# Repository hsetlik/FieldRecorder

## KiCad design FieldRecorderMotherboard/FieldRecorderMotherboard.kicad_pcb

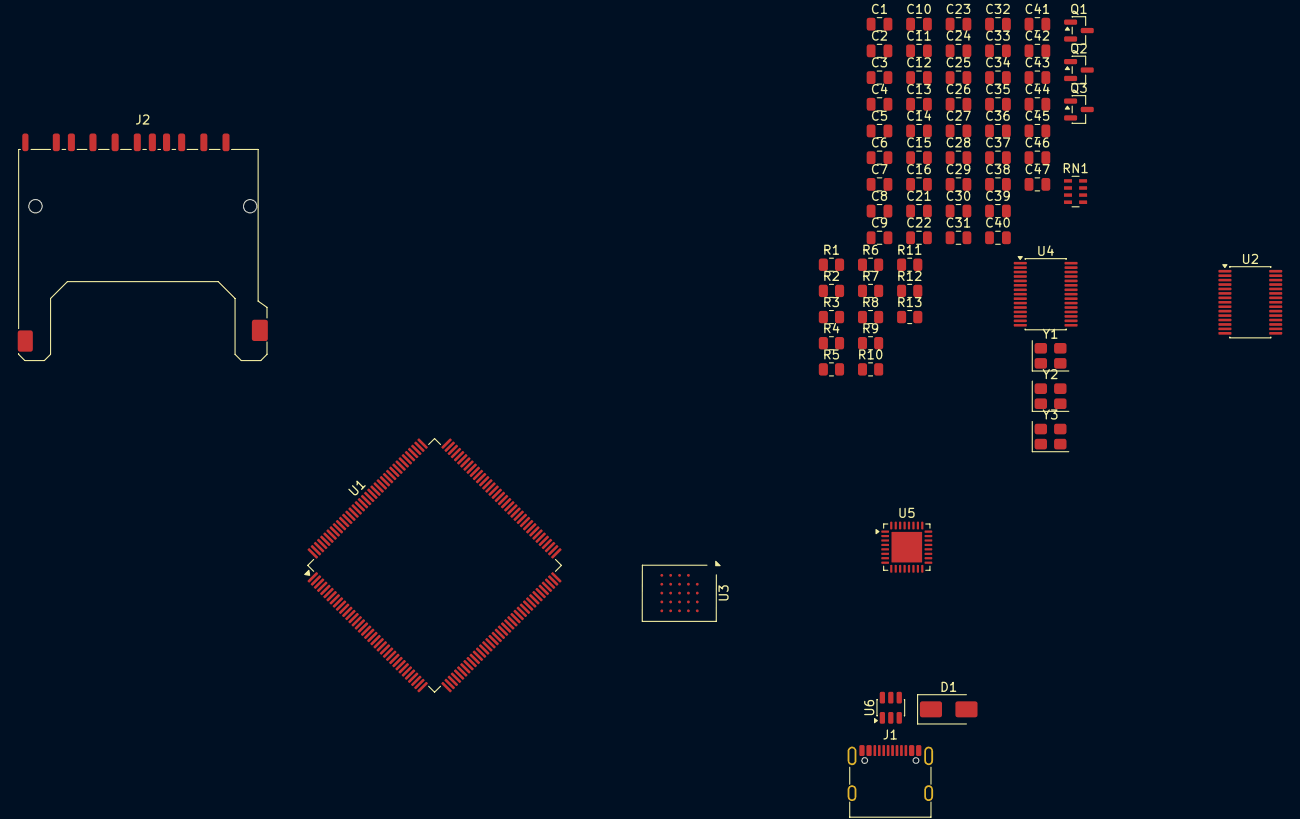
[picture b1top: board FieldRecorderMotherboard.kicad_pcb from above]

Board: 2 copper layers, 72 parts (0 on the bottom side), 67 nets, no tracks yet.

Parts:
C1, C4, C6, C9, C11, C12, C13, C14, C25, C26, C27, C28, C31, C32, C34, C35, C36, C37, C38, C39, C40, C41, C42, C43, C44, C45, C46: 1u; C_0805_2012Metric
C2, C7: 100n; C_0805_2012Metric
C3, C5, C8, C10, C47: 10u; C_0805_2012Metric
C15, C16: 2u2; C_0805_2012Metric
C21, C22, C23, C24, C29, C30: 6p; C_0805_2012Metric
C33: 4n7; C_0805_2012Metric
D1: SMAJ5.0A; D_SMA
J1: USB_C_Receptacle_USB2.0_16P; USB_C_Receptacle_G-Switch_GT-USB-7010ASV
J2: SD_Card_Receptacle; SD_Kyocera_145638009211859+
Q1: MMFTP3401; SOT-23
Q2, Q3: 2N7002; SOT-23
R1, R2: 2k2; R_0805_2012Metric
R3: 12.0k 1%; R_0805_2012Metric
R4: 820; R_0805_2012Metric
R5, R6: 5k1; R_0805_2012Metric
R7: 1Meg; R_0805_2012Metric
R8: 0R; R_0805_2012Metric
R9: 47; R_0805_2012Metric
R10: 100k; R_0805_2012Metric
R11: 100; R_0805_2012Metric
R12, R13: 22k; R_0805_2012Metric
RN1: 22k; R_Array_Concave_4x0603
U1: STM32H723ZGTx; LQFP-144_20x20mm_P0.5mm
U2, U4: PCM1864DBT; TSSOP-30_4.4x7.8mm_P0.5mm
U3: APS12808L; miniBGA-24_6x8mm_Layout5x5_P1.0mm
U5: USB3300-EZK; QFN-32-1EP_5x5mm_P0.5mm_EP3.45x3.45mm
U6: USBLC6-2SC6; SOT-23-6
Y1, Y2: 16MHz; Crystal_SMD_3225-4Pin_3.2x2.5mm
Y3: 24Mhz; Crystal_SMD_3225-4Pin_3.2x2.5mm

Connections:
+3.3V: C4.1, C5.1, C9.1, C10.1, C13.1, C14.1, C25.2, C26.2, C34.2, C35.2, C36.2, C37.2, C38.2, C39.2, C40.2, C41.2, C42.2, C43.2, C44.2, C45.2, Q1.3 (D), R1.1, R2.1, R9.1, R10.1, R13.1, U1.6 (VBAT), U1.17 (VDD), U1.30 (VDD), U1.39 (VDD), U1.52 (VDD), U1.62 (VDD), U1.72 (VDD), U1.84 (VDD), U1.95 (VDD33USB), U1.108 (VDD), U1.121 (VDD), U1.131 (VDD), U1.144 (VDD), U2.13 (DVDD), U2.14 (IOVDD), U3.B4 (VDD), U3.D1 (VDDQ), U3.E4 (VDDQ), U4.13 (DVDD), U4.14 (IOVDD), U4.25 (MS/AD), U5.6 (VDD3.3), U5.16 (VDD3.3), U5.25 (VDD3.3), U5.30 (VDD3.3), U5.31 (REG_EN)
+3.3VA: C1.1, C6.1, C46.2, C47.2, R9.2, U1.33 (VDDA), U2.8 (AVDD), U4.8 (AVDD)
/AudioMCU/ADC_BCK: U1.4 (PE5), U2.17 (BCK), U4.17 (BCK)
/AudioMCU/ADC_DATA: U1.5 (PE6), U2.18 (DOUT), U4.18 (DOUT)
/AudioMCU/ADC_LRCK: U1.3 (PE4), U2.16 (LRCK), U4.16 (LRCK)
/AudioMCU/ADC_SCL: R1.2, U1.136 (PB6), U2.24 (MC/SCL), U4.24 (MC/SCL)
/AudioMCU/ADC_SDA: R2.2, U1.137 (PB7), U2.23 (MOSI/SDA), U4.23 (MOSI/SDA)
/AudioMCU/MEM_CLK: U1.48 (PB2), U3.B2 (CLK)
/AudioMCU/MEM_DQS: U1.35 (PA1), U3.C3 (DQS)
/AudioMCU/MEM_IO0: U1.80 (PD11), U3.D3 (ADQ0)
/AudioMCU/MEM_IO1: U1.81 (PD12), U3.D2 (ADQ1)
/AudioMCU/MEM_IO2: U1.43 (PA7), U3.C4 (ADQ2)
/AudioMCU/MEM_IO3: U1.82 (PD13), U3.D4 (ADQ3)
/AudioMCU/MEM_IO4: U1.58 (PE7), U3.D5 (ADQ4)
/AudioMCU/MEM_IO5: U1.59 (PE8), U3.E3 (ADQ5)
/AudioMCU/MEM_IO6: U1.60 (PE9), U3.E2 (ADQ6)
/AudioMCU/MEM_IO7: U1.63 (PE10), U3.E1 (ADQ7)
/AudioMCU/MEM_NCS: U1.64 (PE11), U3.A3 (CE)
/AudioMCU/MEM_RST: U1.65 (PE12), U3.A4 (RST)
/AudioMCU/SD_CK: J2.5 (CLK), U1.122 (PD6)
/AudioMCU/SD_CMD: J2.2 (CMD), R12.2, U1.123 (PD7)
/AudioMCU/SD_D0: J2.7 (DAT0), RN1.1 (R1.1), U1.124 (PG9)
/AudioMCU/SD_D1: J2.8 (DAT1), RN1.2 (R2.1), U1.125 (PG10)
/AudioMCU/SD_D2: J2.9 (DAT2), RN1.3 (R3.1), U1.126 (PG11)
/AudioMCU/SD_D3: J2.1 (CD/DAT3), RN1.4 (R4.1), U1.127 (PG12)
/AudioMCU/SD_DETECT: J2.10 (CARD_DETECT), R13.2, U1.128 (PG13)
/AudioMCU/SD_PWR: Q2.1 (G), U1.129 (PG14)
/AudioMCU/USB_CK: U1.41 (PA5), U5.14 (CLKOUT)
/AudioMCU/USB_D0: U1.37 (PA3), U5.24 (DATA0)
/AudioMCU/USB_D1: U1.46 (PB0), U5.23 (DATA1)
/AudioMCU/USB_D2: U1.47 (PB1), U5.22 (DATA2)
/AudioMCU/USB_D3: U1.69 (PB10), U5.21 (DATA3)
/AudioMCU/USB_D4: U1.70 (PB11), U5.20 (DATA4)
/AudioMCU/USB_D5: U1.73 (PB12), U5.19 (DATA5)
/AudioMCU/USB_D6: U1.74 (PB13), U5.18 (DATA6)
/AudioMCU/USB_D7: U1.135 (PB5), U5.17 (DATA7)
/AudioMCU/USB_D+: U5.7 (DP), U6.4 (I/O2)
/AudioMCU/USB_D-: U5.8 (DM), U6.6 (I/O1)
/AudioMCU/USB_DIR: U1.28 (PC2_C), U5.12 (DIR)
/AudioMCU/USB_NXT: U1.29 (PC3_C), U5.11 (NXT)
/AudioMCU/USB_STP: U1.26 (PC0), U5.13 (STP)
GND: C1.2, C2.2, C3.2, C4.2, C5.2, C6.2, C7.2, C8.2, C9.2, C10.2, C11.2, C12.2, C13.2, C14.2, C15.2, C16.2, C21.1, C22.1, C23.1, C24.1, C25.1, C26.1, C27.1, C28.1, C29.1, C30.1, C31.1, C32.1, C33.1, C34.1, C35.1, C36.1, C37.1, C38.1, C39.1, C40.1, C41.1, C42.1, C43.1, C44.1, C45.1, C46.1, C47.1, D1.2 (A2), J1.A1 (GND), J1.A12 (GND), J1.B1 (GND), J1.B12 (GND), J2.3 (VSS), J2.6 (VSS), Q2.2 (S), Q3.2 (S), R3.2, R5.2, R6.2, R7.2, R8.2, U1.16 (VSS), U1.31 (VSSA), U1.38 (VSS), U1.51 (VSS), U1.61 (VSS), U1.83 (VSS), U1.94 (VSS), U1.107 (VSS), U1.120 (VSS), U1.130 (VSS), U2.7 (AGND), U2.12 (DGND), U2.25 (MS/AD), U2.26 (MD0), U3.B3 (VSS), U3.C1 (VSSQ), U3.E5 (VSSQ), U4.7 (AGND), U4.12 (DGND), U4.26 (MD0), U5.1 (GND), U5.2 (GND), U5.9 (RESET), U5.33 (GND), U6.2 (GND), Y1.2 (G), Y1.4 (G), Y2.2 (G), Y2.4 (G), Y3.2 (G), Y3.4 (G)
unnamed: C15.1, U1.106 (VCAP)
unnamed: C16.1, U1.71 (VCAP)
unnamed: C31.2, U5.15 (VDD1.8), U5.26 (VDD1.8)
unnamed: J1.A5 (CC1), R6.1
unnamed: J1.B5 (CC2), R5.1
unnamed: J1.A6 (D+), J1.B6 (D+), U6.3 (I/O2)
unnamed: J1.A7 (D-), J1.B7 (D-), U6.1 (I/O1)
unnamed: C33.2, J1.SH (SHIELD), R7.1, R8.1
unnamed: Q1.1 (G), Q2.3 (D), Q3.1 (G), R10.2
unnamed: Q3.3 (D), R11.2
unnamed: C23.2, U1.23 (PH0), Y2.1
unnamed: C24.2, U1.24 (PH1), Y2.3
unnamed: C2.1, C3.1, U2.11 (LDO)
unnamed: C11.1, U2.6 (VREF)
unnamed: C22.2, U2.10 (XI), Y1.3
unnamed: C21.2, U2.9 (XO), Y1.1
unnamed: C7.1, C8.1, U4.11 (LDO)
unnamed: C12.1, U4.6 (VREF)
unnamed: R3.1, U5.32 (RBIAS)
unnamed: R4.2, U5.4 (VBUS)
unnamed: C32.2, U5.29 (VDDA1.8)
unnamed: C30.2, U5.28 (XI), Y3.3
unnamed: C29.2, U5.27 (XO), Y3.1
USB_VBUS: C27.2, D1.1 (A1), J1.A4 (VBUS), J1.A9 (VBUS), J1.B4 (VBUS), J1.B9 (VBUS), R4.1, U6.5 (VBUS)
VCC_SD: C28.2, J2.4 (VDD), Q1.2 (S), R11.1, R12.1, RN1.5 (R4.2), RN1.6 (R3.2), RN1.7 (R2.2), RN1.8 (R1.2)

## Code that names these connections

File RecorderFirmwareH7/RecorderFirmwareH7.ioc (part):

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Mcu.Name=STM32H723ZGTx
Mcu.Package=LQFP144
Mcu.UserName=STM32H723ZGTx
PA1.Mode=OCTOSPI2_Port1_DQS
PA1.Signal=OCTOSPIM_P1_DQS
PA13(JTMS/SWDIO).Mode=Serial_Wire
PA13(JTMS/SWDIO).Signal=DEBUG_JTMS-SWDIO
PA14(JTCK/SWCLK).Mode=Serial_Wire
PA14(JTCK/SWCLK).Signal=DEBUG_JTCK-SWCLK
PA3.Mode=Device_HS
PA3.Signal=USB_OTG_HS_ULPI_D0
PA5.Mode=Device_HS
PA5.Signal=USB_OTG_HS_ULPI_CK
PA7.Mode=OCTOSPI2_IOL_Port1L
PA7.Signal=OCTOSPIM_P1_IO2
PB0.Mode=Device_HS
PB0.Signal=USB_OTG_HS_ULPI_D1
PB1.Mode=Device_HS
PB1.Signal=USB_OTG_HS_ULPI_D2
PB10.Mode=Device_HS
PB10.Signal=USB_OTG_HS_ULPI_D3
PB11.Mode=Device_HS
PB11.Signal=USB_OTG_HS_ULPI_D4
PB12.Mode=Device_HS
PB12.Signal=USB_OTG_HS_ULPI_D5
PB13.Mode=Device_HS
PB13.Signal=USB_OTG_HS_ULPI_D6
PB2.Mode=O2_P1_CLK
PB2.Signal=OCTOSPIM_P1_CLK
PB5.Mode=Device_HS
PB5.Signal=USB_OTG_HS_ULPI_D7
PB6.GPIOParameters=GPIO_Label
PB6.GPIO_Label=ADC_SCL
PB6.Mode=I2C
PB6.Signal=I2C1_SCL
PB7.GPIOParameters=GPIO_Label
PB7.GPIO_Label=ADC_SDA
PB7.Mode=I2C
PB7.Signal=I2C1_SDA
PC0.Mode=Device_HS
PC0.Signal=USB_OTG_HS_ULPI_STP
PC12.Mode=Asynchronous
PC12.Signal=UART5_TX
PC2_C.Mode=Device_HS
PC2_C.Signal=USB_OTG_HS_ULPI_DIR
PC3_C.Mode=Device_HS
PC3_C.Signal=USB_OTG_HS_ULPI_NXT
PD11.Mode=OCTOSPI2_IOL_Port1L
PD11.Signal=OCTOSPIM_P1_IO0
PD12.Mode=OCTOSPI2_IOL_Port1L
PD12.Signal=OCTOSPIM_P1_IO1
PD13.Mode=OCTOSPI2_IOL_Port1L
PD13.Signal=OCTOSPIM_P1_IO3
PD2.Mode=Asynchronous
PD2.Signal=UART5_RX
PD3.GPIOParameters=GPIO_Label
PD3.GPIO_Label=UI_NRST
PD3.Signal=GPIO_Output
PD4.GPIOParameters=GPIO_Label
PD4.GPIO_Label=UI_BOOT0
PD4.Signal=GPIO_Output
PD6.GPIOParameters=GPIO_Label
PD6.GPIO_Label=SD_CK
PD6.Mode=SD_4_bits_Wide_bus
PD6.Signal=SDMMC2_CK
PD7.GPIOParameters=GPIO_Label
PD7.GPIO_Label=SD_CMD
PD7.Mode=SD_4_bits_Wide_bus
PD7.Signal=SDMMC2_CMD
PE10.Mode=OCTOSPI2_IOH_Port1H
PE10.Signal=OCTOSPIM_P1_IO7
PE11.Mode=OCTOSPI2_Port1_NCS
PE11.Signal=OCTOSPIM_P1_NCS
PE12.GPIOParameters=GPIO_Label
PE12.GPIO_Label=OCTOSPI_RST
PE12.Signal=GPIO_Output
PE4.GPIOParameters=GPIO_Label
PE4.GPIO_Label=ADC_LRCK
PE4.Mode=SAI_A_AsyncSlave
PE4.Signal=SAI1_FS_A
PE5.GPIOParameters=GPIO_Label
PE5.GPIO_Label=ADC_BCK
PE5.Mode=SAI_A_AsyncSlave
PE5.Signal=SAI1_SCK_A
PE6.GPIOParameters=GPIO_Label
PE6.GPIO_Label=ADC_DATA
PE6.Mode=SAI_A_AsyncSlave
PE6.Signal=SAI1_SD_A
PE7.Mode=OCTOSPI2_IOH_Port1H
PE7.Signal=OCTOSPIM_P1_IO4
PE8.Mode=OCTOSPI2_IOH_Port1H
PE8.Signal=OCTOSPIM_P1_IO5
PE9.Mode=OCTOSPI2_IOH_Port1H
PE9.Signal=OCTOSPIM_P1_IO6
PG10.GPIOParameters=GPIO_Label
PG10.GPIO_Label=SD_D1
PG10.Mode=SD_4_bits_Wide_bus
PG10.Signal=SDMMC2_D1
PG11.GPIOParameters=GPIO_Label
PG11.GPIO_Label=SD_D2
PG11.Mode=SD_4_bits_Wide_bus
PG11.Signal=SDMMC2_D2
PG12.GPIOParameters=GPIO_Label
PG12.GPIO_Label=SD_D3
PG12.Mode=SD_4_bits_Wide_bus
PG12.Signal=SDMMC2_D3
PG13.GPIOParameters=GPIO_Label
PG13.GPIO_Label=SD_DETECT
PG13.Signal=GPIO_Input
PG14.GPIOParameters=GPIO_Label
PG14.GPIO_Label=SD_PWR
PG14.Signal=GPIO_Output
PG9.GPIOParameters=GPIO_Label
PG9.GPIO_Label=SD_D0
PG9.Mode=SD_4_bits_Wide_bus
PG9.Signal=SDMMC2_D0
PH0-OSC_IN.Mode=HSE-External-Oscillator
PH0-OSC_IN.Signal=RCC_OSC_IN
PH1-OSC_OUT.Mode=HSE-External-Oscillator
PH1-OSC_OUT.Signal=RCC_OSC_OUT
RCC.HSE_VALUE=16000000
RCC.SYSCLKFreq_VALUE=192000000
RCC.SYSCLKSource=RCC_SYSCLKSOURCE_PLLCLK
board=custom
